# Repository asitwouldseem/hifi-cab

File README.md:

# hifi-cab
A KiCAD project for a temperature controlled fan (et al).

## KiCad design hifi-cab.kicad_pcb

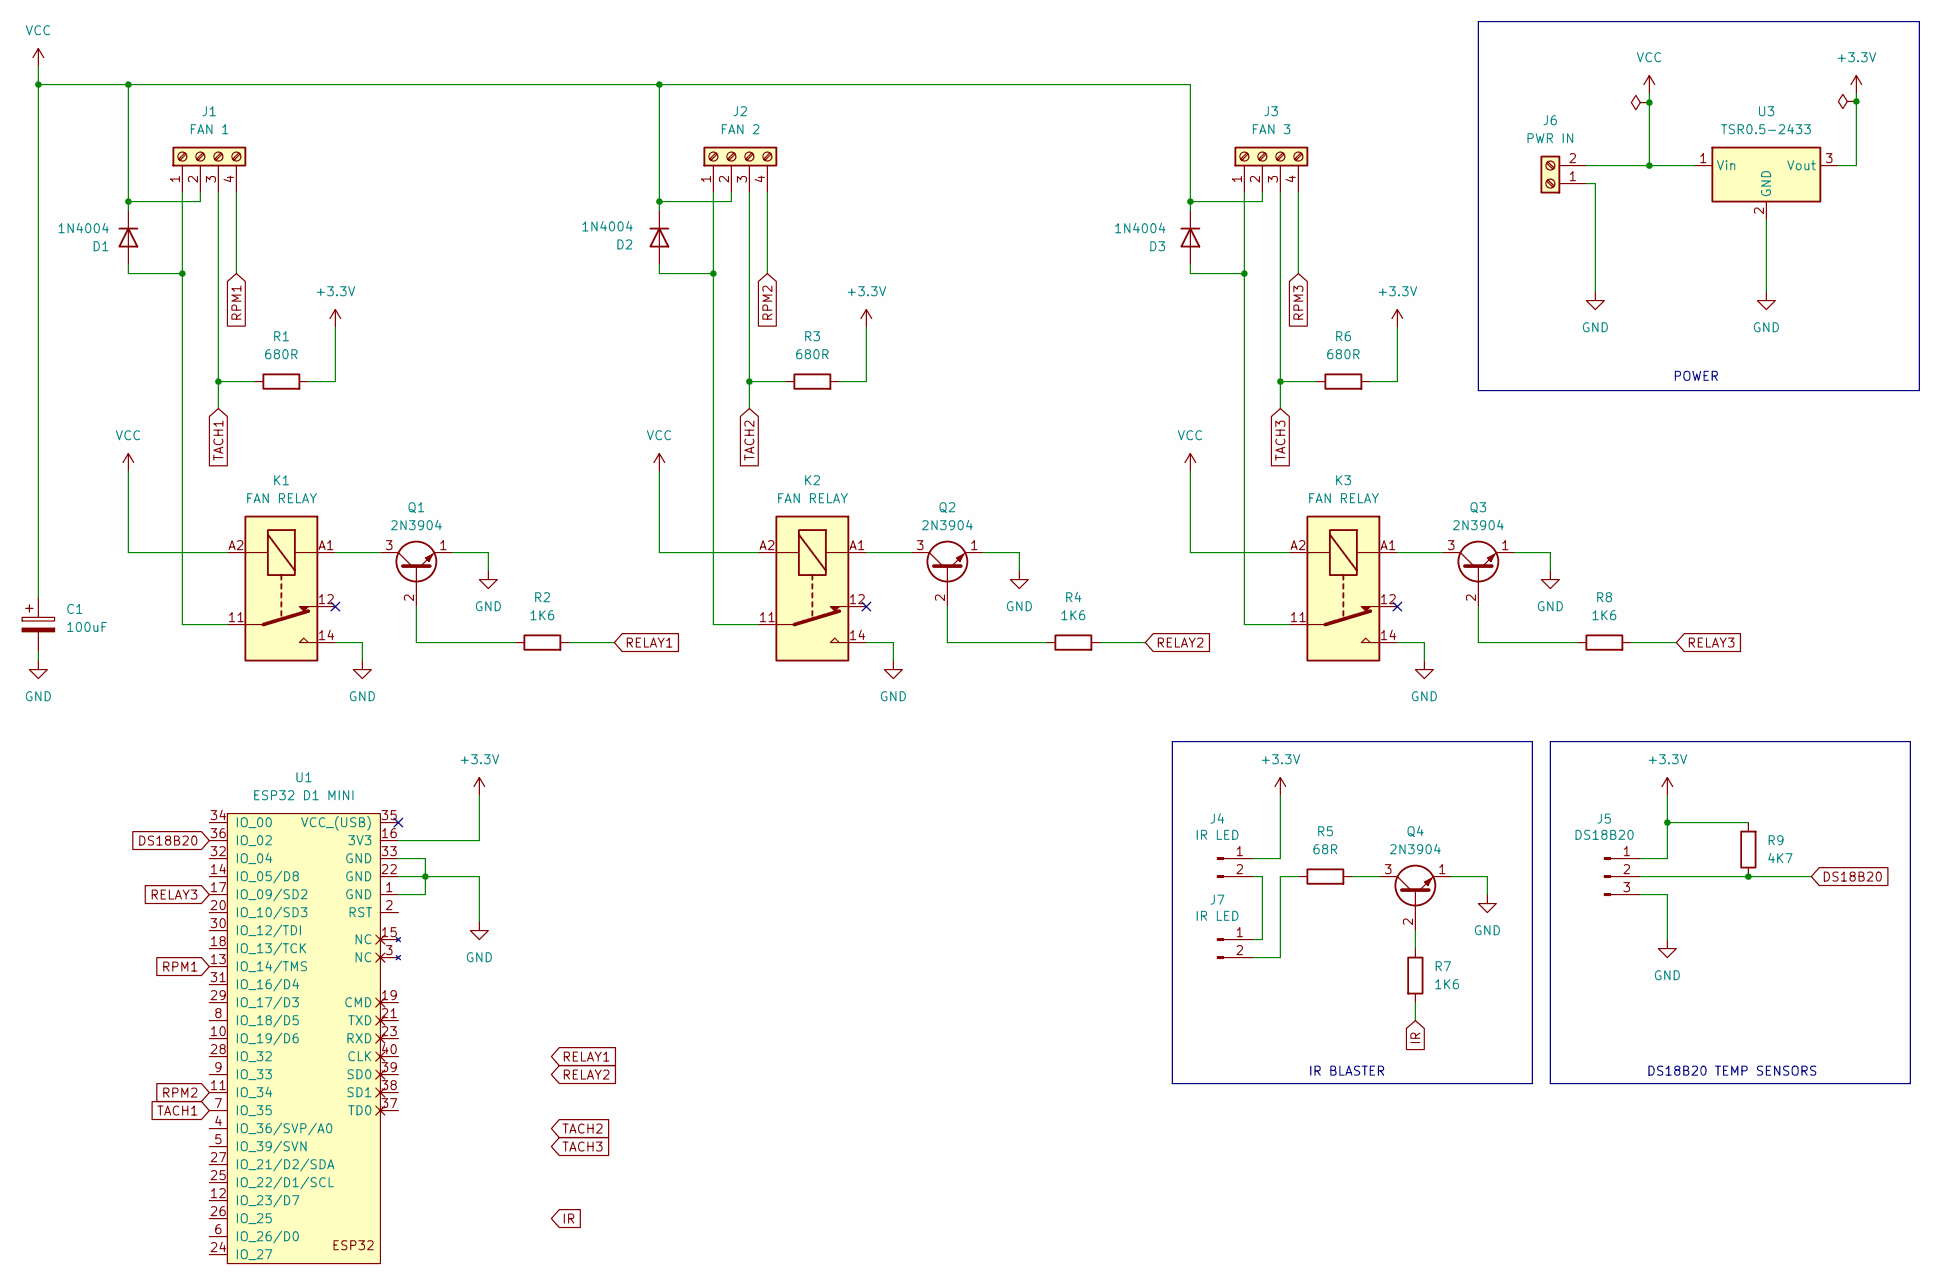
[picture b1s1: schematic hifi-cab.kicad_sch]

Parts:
C1: 100uF; CP_Radial_D6.3mm_P2.50mm
D1, D2, D3: 1N4004; D_DO-41_SOD81_P10.16mm_Horizontal
J1: FAN 1; FanPinHeader_1x04_P2.54mm_Vertical
J2: FAN 2; FanPinHeader_1x04_P2.54mm_Vertical
J3: FAN 3; FanPinHeader_1x04_P2.54mm_Vertical
J4, J7: IR LED; JST_XH_B2B-XH-A_1x02_P2.50mm_Vertical
J5: DS18B20; JST_XH_B3B-XH-A_1x03_P2.50mm_Vertical
J6: PWR IN; JST_XH_B2B-XH-A_1x02_P2.50mm_Vertical
K1, K2, K3: FAN RELAY; RELAY_SR5-12V-200-1C
Q1, Q2, Q3, Q4: 2N3904; TO-92_Inline
R1, R3, R6: 680R; R_Axial_DIN0204_L3.6mm_D1.6mm_P7.62mm_Horizontal
R2, R4, R7, R8: 1K6; R_Axial_DIN0204_L3.6mm_D1.6mm_P7.62mm_Horizontal
R5: 68R; R_Axial_DIN0204_L3.6mm_D1.6mm_P7.62mm_Horizontal
R9: 4K7; R_Axial_DIN0204_L3.6mm_D1.6mm_P7.62mm_Horizontal
U1: ESP32 D1 MINI; esp32-wemos-d1-mini
U3: TSR0.5-2433; Converter_DCDC_TRACO_TSR0.5-24xx_TSR0.5-24xxx_THT

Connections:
+3.3V: J4.1, J5.1, R1.2, R3.2, R6.2, R9.2, U1.16 (3V3), U3.3 (Vout)
DS18B20: J5.2, R9.1, U1.36 (IO_02)
GND: C1.2, J5.3, J6.1, K1.14, K2.14, K3.14, Q1.1 (E), Q2.1 (E), Q3.1 (E), Q4.1 (E), U1.1 (GND), U1.22 (GND), U1.33 (GND), U3.2 (GND)
IR: R7.2
unnamed: D1.2 (A), J1.1, K1.11
unnamed: D2.2 (A), J2.1, K2.11
unnamed: D3.2 (A), J3.1, K3.11
unnamed: J4.2, J7.1
unnamed: J7.2, R5.1
unnamed: Q1.2 (B), R2.1
unnamed: K1.A1, Q1.3 (C)
unnamed: Q2.2 (B), R4.1
unnamed: K2.A1, Q2.3 (C)
unnamed: Q3.2 (B), R8.1
unnamed: K3.A1, Q3.3 (C)
unnamed: Q4.2 (B), R7.1
unnamed: Q4.3 (C), R5.2
RELAY1: R2.2
RELAY2: R4.2
RELAY3: R8.2, U1.17 (IO_09/SD2)
RPM1: J1.4, U1.13 (IO_14/TMS)
RPM2: J2.4, U1.11 (IO_34)
RPM3: J3.4
TACH1: J1.3, R1.1, U1.7 (IO_35)
TACH2: J2.3, R3.1
TACH3: J3.3, R6.1
VCC: C1.1, D1.1 (K), D2.1 (K), D3.1 (K), J1.2, J2.2, J3.2, J6.2, K1.A2, K2.A2, K3.A2, U3.1 (Vin)

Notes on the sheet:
POWER
IR BLASTER
DS18B20 TEMP SENSORS

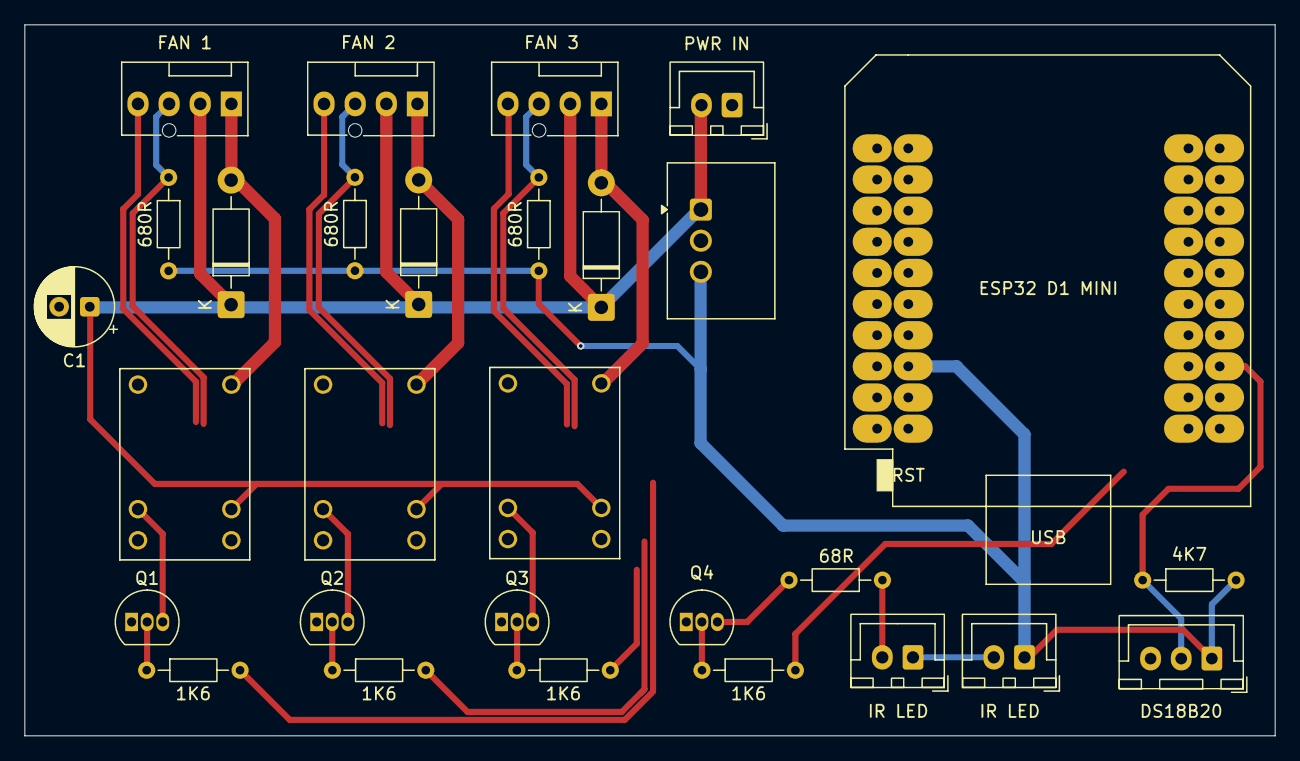
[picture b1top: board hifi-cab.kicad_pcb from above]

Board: 2 copper layers, 102.0 x 58.0 mm, 29 parts (0 on the bottom side), 23 nets.

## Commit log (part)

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2026-03-06 init
2026-03-06 Add RJ45
2026-03-08 V1 schematic
2026-03-08 Switch some low current connectors to JSTs.
2026-03-08 Jumper on input voltage.
2026-03-08 Add note.
2026-03-08 Start assigning footprints.
2026-03-13 Update schematic.
2026-03-13 Start layout
2026-03-13 Moar layout
2026-03-14 Simplify, return to 5V only.
2026-03-14 Add cap
2026-03-14 Fix power on schematic
2026-03-15 Explore layout.
2026-03-15 Default to old habits.
2026-03-15 Enough for tonight.
2026-03-15 I lied, for real now. Enough for today.
2026-03-28 Tidy footprints
2026-05-31 More layout
2026-05-31 Power routing complete
2026-05-31 Start routing signals
2026-05-31 Add silkscreen R9
2026-06-20 Start DRC
2026-06-21 Ready for prod V3.1
2026-06-21 Bump up 3.3V trace
2026-06-21 Fix pin selection
2026-06-26 Change C1 footprint
